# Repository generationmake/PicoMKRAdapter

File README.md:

# PicoMKRAdapter
adapter board to connect a Raspberry Pi Pico to an Arduino MKR Shield and vice versa

### Raspberry Pi Pico Side

### Arduino MKR Side

## pin usage

### Arduino MKR connector CN2 vs Raspberry Pi Pico connector CN1

| **Pin** | **Pin Name** | **Pin Name**      | **Pin**                                |
|:-------:|:------------:|:-----------------:|:--------------------------------------:|
| x  | **Arduino MKR**   | **Raspberry Pi Pico**                                 |  x |
| 1       | AREF         | ADC_VREF          | 35                                     |
| 2       | DAC0/A0      | GP26/ADC0         | 31                                     |
| 3       | A1           | GP27/ADC1         | 32                                     |
| 4       | A2           | GP28/ADC2         | 34                                     |
| 5       | A3           | GP15              | 20                                     |
| 6       | A4           | GP22              | 29                                     |
| 7       | A5           | GP21              | 27                                     |
| 8       | A6           | GP20              | 26                                     |
| 9       | 0            | GP0               | 1                                      |
| 10      | 1            | GP1               | 2                                      |
| 11      | 2            | GP2               | 4                                      |
| 12      | 3            | GP3               | 5                                      |
| 13      | 4            | GP10              | 14                                     |
| 14      | 5            | GP5               | 7                                      |
| 15      | 6            | GP14              | 19                                     |
| 16      | 7            | GP11              | 15                                     |
| 17      | 8/MOSI       | GP7               | 10                                     |
| 18      | 9/SCK        | GP6               | 9                                      |
| 19      | 10/MISO      | GP4               | 6                                      |
| 20      | 11/SDA       | GP12/I2C0_SDA     | 16                                     |
| 21      | 12/SCL       | GP13/I2C0_SCL     | 17                                     |
| 22      | 13/RX        | GP9/UART1_RX      | 12                                     |
| 23      | 14/TX        | GP8/UART1_TX      | 11                                     |
| 24      | RESET        | RUN               | 30                                     |
| 25      | GND          | GND               | 3..38                                  |
| 26      | VCC          | 3V3               | 36                                     |
| 27      | VIN          | VBUS              | 40                                     |
| 28      | 5V0          | VSYS              | 39                                     |

## PCB

### Top

### Bottom

## License

This hardware is licensed under the CERN OHL v. 1.2

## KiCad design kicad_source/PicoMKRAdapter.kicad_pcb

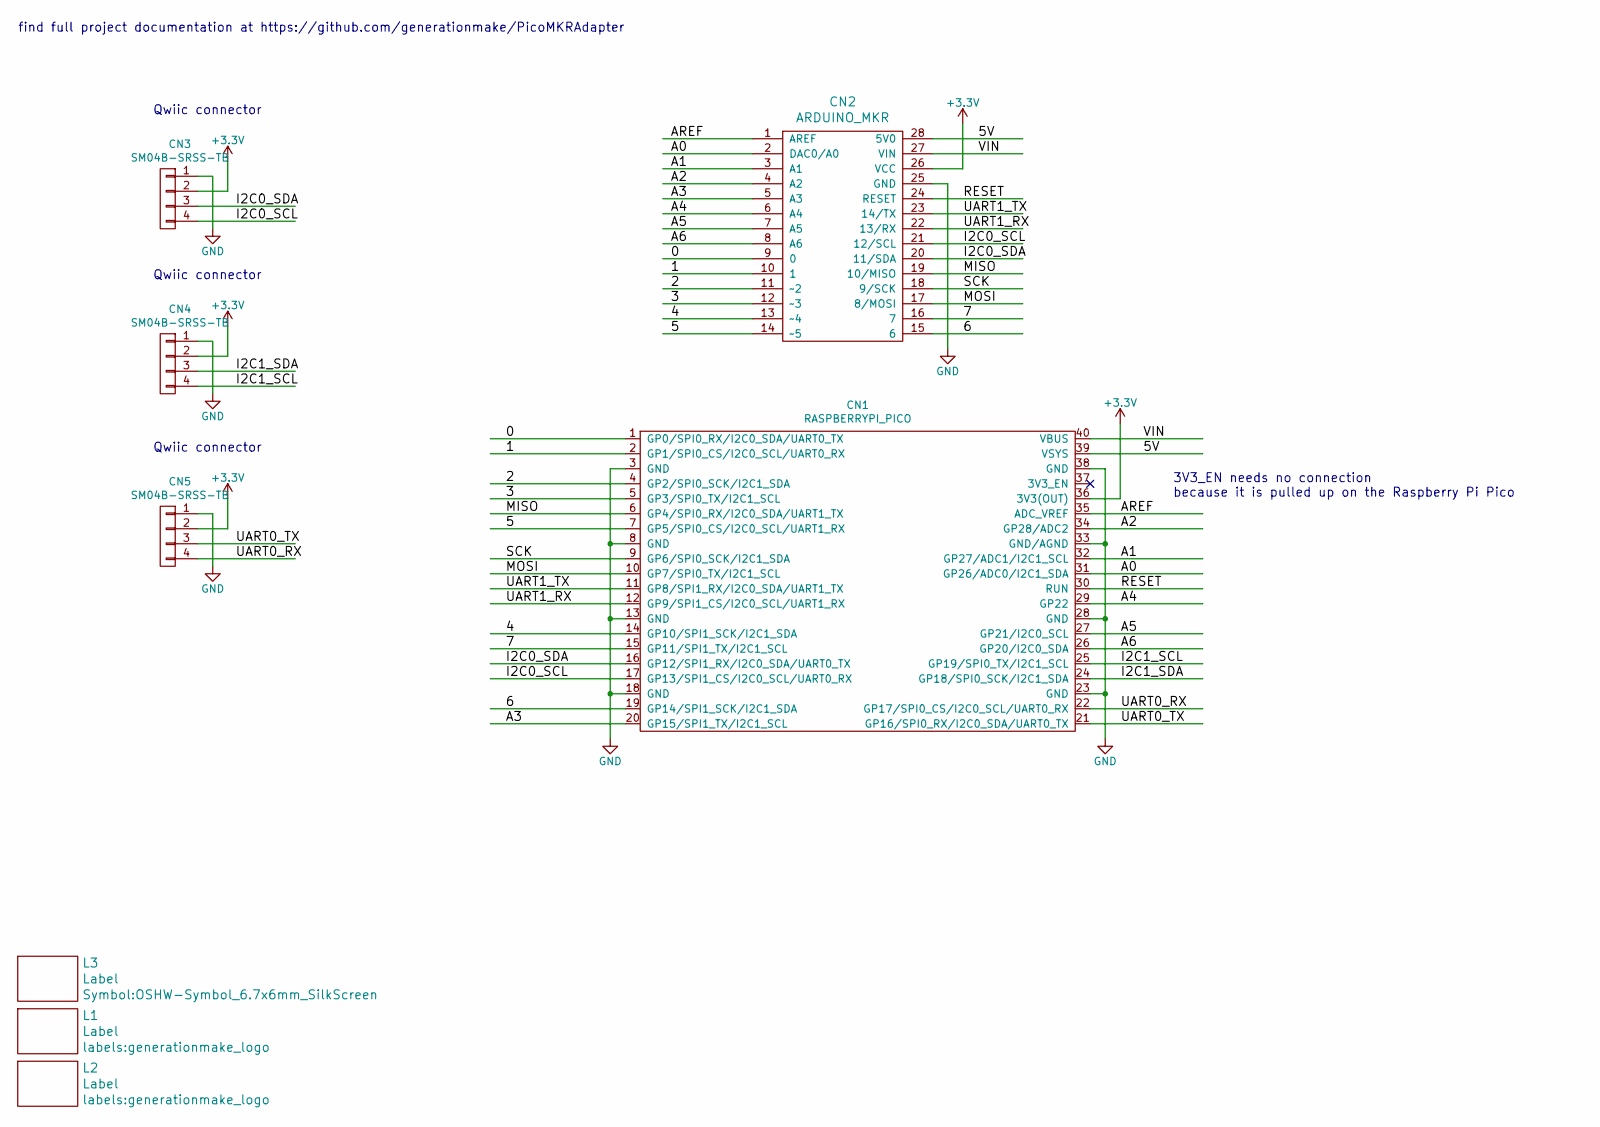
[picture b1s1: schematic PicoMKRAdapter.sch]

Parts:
CN1: RASPBERRYPI_PICO; RASPI_PICO
CN2: ARDUINO_MKR; ARDUINO_MKR_BASEBOARD
CN3, CN4, CN5: SM04B-SRSS-TB; Connectors_JST_SM04B-SRSS-TB
L1, L2: Label; generationmake_logo
L3: Label; OSHW-Symbol_6.7x6mm_SilkScreen

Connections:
+3V3: CN1.36 (3V3(OUT)), CN2.26 (VCC), CN3.2, CN4.2, CN5.2
/0: CN1.1 (GP0/SPI0_RX/I2C0_SDA/UART0_TX), CN2.9 (0)
/1: CN1.2 (GP1/SPI0_CS/I2C0_SCL/UART0_RX), CN2.10 (1)
/2: CN1.4 (GP2/SPI0_SCK/I2C1_SDA), CN2.11 (~~2)
/3: CN1.5 (GP3/SPI0_TX/I2C1_SCL), CN2.12 (~~3)
/4: CN1.14 (GP10/SPI1_SCK/I2C1_SDA), CN2.13 (~~4)
/5: CN1.7 (GP5/SPI0_CS/I2C0_SCL/UART1_RX), CN2.14 (~~5)
/5V: CN1.39 (VSYS), CN2.28 (5V0)
/6: CN1.19 (GP14/SPI1_SCK/I2C1_SDA), CN2.15 (6)
/7: CN1.15 (GP11/SPI1_TX/I2C1_SCL), CN2.16 (7)
/A0: CN1.31 (GP26/ADC0/I2C1_SDA), CN2.2 (DAC0/A0)
/A1: CN1.32 (GP27/ADC1/I2C1_SCL), CN2.3 (A1)
/A2: CN1.34 (GP28/ADC2), CN2.4 (A2)
/A3: CN1.20 (GP15/SPI1_TX/I2C1_SCL), CN2.5 (A3)
/A4: CN1.29 (GP22), CN2.6 (A4)
/A5: CN1.27 (GP21/I2C0_SCL), CN2.7 (A5)
/A6: CN1.26 (GP20/I2C0_SDA), CN2.8 (A6)
/AREF: CN1.35 (ADC_VREF), CN2.1 (AREF)
/I2C0_SCL: CN1.17 (GP13/SPI1_CS/I2C0_SCL/UART0_RX), CN2.21 (12/SCL), CN3.4
/I2C0_SDA: CN1.16 (GP12/SPI1_RX/I2C0_SDA/UART0_TX), CN2.20 (11/SDA), CN3.3
/I2C1_SCL: CN1.25 (GP19/SPI0_TX/I2C1_SCL), CN4.4
/I2C1_SDA: CN1.24 (GP18/SPI0_SCK/I2C1_SDA), CN4.3
/MISO: CN1.6 (GP4/SPI0_RX/I2C0_SDA/UART1_TX), CN2.19 (10/MISO)
/MOSI: CN1.10 (GP7/SPI0_TX/I2C1_SCL), CN2.17 (8/MOSI)
/RESET: CN1.30 (RUN), CN2.24 (RESET)
/SCK: CN1.9 (GP6/SPI0_SCK/I2C1_SDA), CN2.18 (9/SCK)
/UART0_RX: CN1.22 (GP17/SPI0_CS/I2C0_SCL/UART0_RX), CN5.4
/UART0_TX: CN1.21 (GP16/SPI0_RX/I2C0_SDA/UART0_TX), CN5.3
/UART1_RX: CN1.12 (GP9/SPI1_CS/I2C0_SCL/UART1_RX), CN2.22 (13/RX)
/UART1_TX: CN1.11 (GP8/SPI1_RX/I2C0_SDA/UART1_TX), CN2.23 (14/TX)
/VIN: CN1.40 (VBUS), CN2.27 (VIN)
GND: CN1.3 (GND), CN1.8 (GND), CN1.13 (GND), CN1.18 (GND), CN1.23 (GND), CN1.28 (GND), CN1.33 (GND/AGND), CN1.38 (GND), CN2.25 (GND), CN3.1, CN4.1, CN5.1

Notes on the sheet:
Qwiic connector
3V3_EN needs no connection because it is pulled up on the Raspberry Pi Pico
find full project documentation at https://github.com/generationmake/PicoMKRAdapter

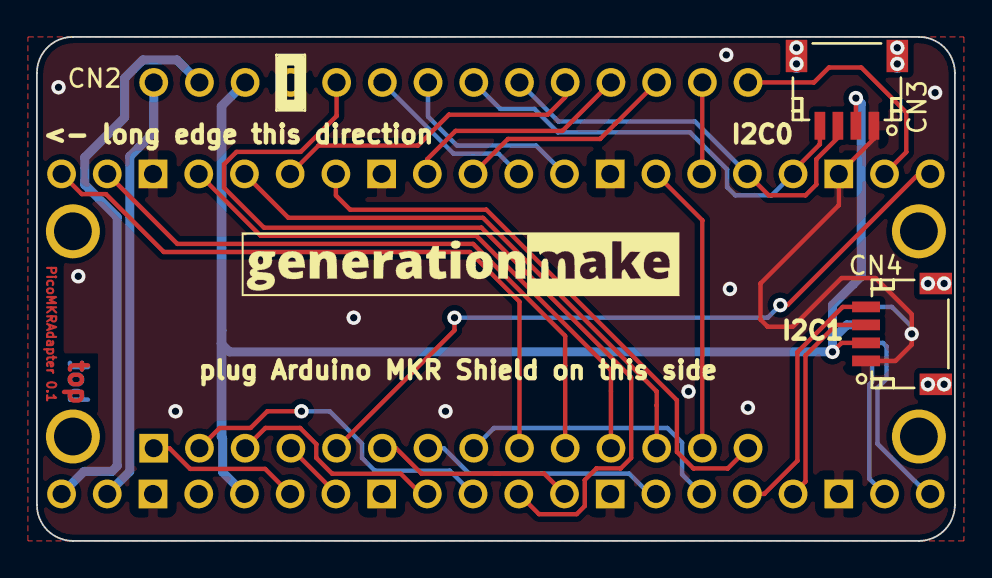
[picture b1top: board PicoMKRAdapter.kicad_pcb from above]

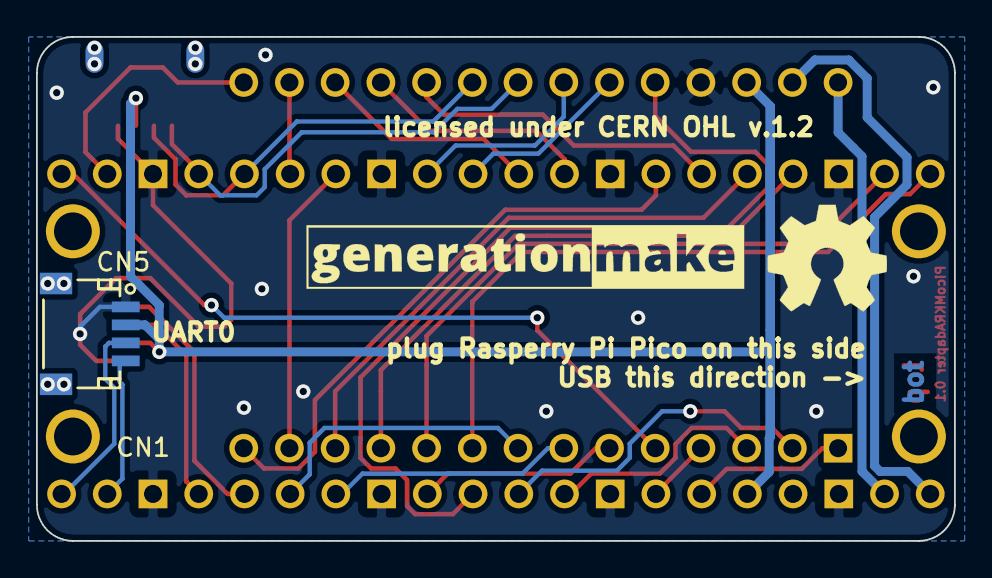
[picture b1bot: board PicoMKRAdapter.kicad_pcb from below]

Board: 2 copper layers, 51.0 x 28.0 mm, 8 parts (4 on the bottom side), 32 nets.

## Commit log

2021-01-23 added kicad project
2021-01-24 added layout
2021-01-24 added schematic pdf
2021-01-24 added some images
2021-01-25 updated layout and schematic, added i2c and serial connectors
2021-01-25 updated schematic pdf and images
2021-01-27 updated pico footprint
2021-01-27 connected RUN to RESET, added some labels
2021-01-27 updated pdfs and images
2021-01-27 added license information
2021-02-12 added info on pin usage

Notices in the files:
kicad_source/PicoMKRAdapter.kicad_pcb:
licensed under CERN OHL v.1.2
